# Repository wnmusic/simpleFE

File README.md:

# simpleFE
A very low cost mixed front end (ADC, DAC, SDR)

## Pre-requisite
simpleFE uses libusb, so a working libusb should be ready. Under linux, libusb also requires udev as the driver interface.  

If you would like to use gr-simplefe, you can install the latest gnuradio, gr-simplefe work as an out of tree module. Make it work on Windows is pretty involved. (please hack the CMakefiles to locate BOOST and CPPUnit)

For libdsp which is continously evolving, fftw3 is a must. 

## Install
```
# cd libsimplefe
# mkdir build
# cd build
# cmake ..
# make
# make install
```

for gr-smiplefe

```
# cd libsimplefe
# mkdir build
# cd build
# cmake ..
# make
# make install
```

## Load the firmware before you go
Right now, the firmware of simplefe is loaded via USB as well. The firmware leaves in firmware directory.  (There is no source for firmware, mainly because it is built based on the example code from Cypress, anyone interested in re-write it using sdcc, please contact me!)

You also have to build the fw\_load (which is done when built libsimplefe), it is in libsimplefe/build/example/fw\_load

```
#cd firmware
#../libsimplfe/build/example/fw\_load simpleFE.hex
```
D6 on simpleFE will be lit if firmware is sucessfuly loaded. 

## Make firmware autoload (Linux)
On linux, the firmware loading can be done by udev. 
```
#mkdir -p /usr/local/share/simplefe
```
Copy fw\_load and simpleFE.hex to /usr/local/share/simplefe. 

Then change 
```
GROUP=`groups | cut -f 1 -d ' '`
``` 
to your own group id by running the command in the quote in udev/99-udev-simplefe.rules. 

After that 
```
#cp udev/99-udev-simplefe.rules /etc/udev/rules.d
```
Next time when you plug in simpleFE D6 will be lit automatically.

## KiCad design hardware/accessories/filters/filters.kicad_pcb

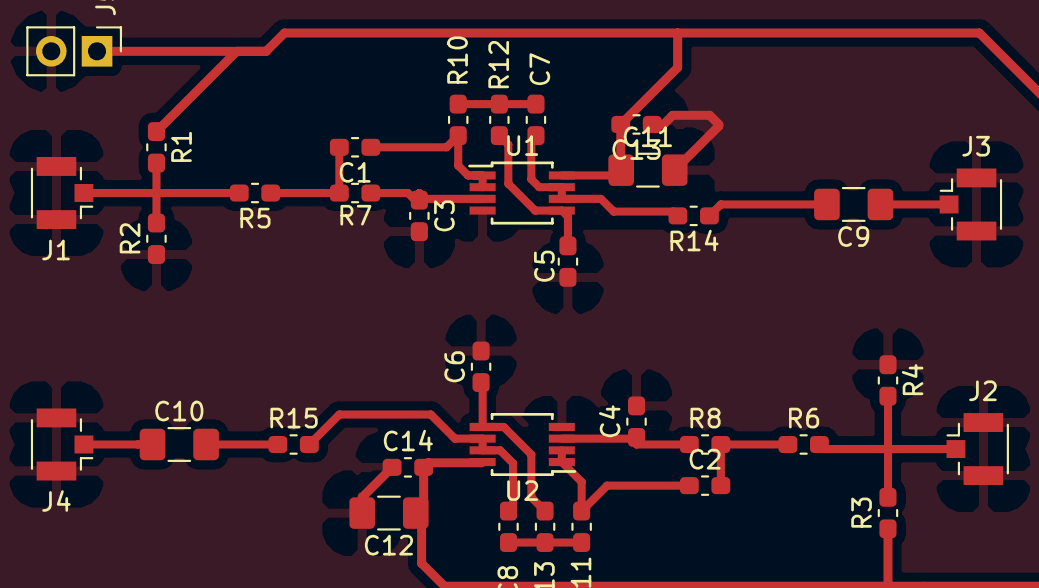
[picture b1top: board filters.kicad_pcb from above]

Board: 2 copper layers, 35 parts (0 on the bottom side), 20 nets.

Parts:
C1, C2: 150p; C_0603_1608Metric_Pad1.05x0.95mm_HandSolder
C3, C4: 120p; C_0603_1608Metric_Pad1.05x0.95mm_HandSolder
C5, C6: 56p; C_0603_1608Metric_Pad1.05x0.95mm_HandSolder
C7, C8: 390p; C_0603_1608Metric_Pad1.05x0.95mm_HandSolder
C9, C10, C11, C12: 10u; C_1206_3216Metric_Pad1.42x1.75mm_HandSolder
C13, C14: 100n; C_0603_1608Metric_Pad1.05x0.95mm_HandSolder
J1, J2, J3, J4: Conn_Coaxial; U.FL_Hirose_U.FL-R-SMT-1_Vertical
J5: PWR; PinHeader_1x02_P2.54mm_Vertical
R1, R2, R3, R4: 100k; R_0603_1608Metric_Pad1.05x0.95mm_HandSolder
R5, R6: 9.1k; R_0603_1608Metric_Pad1.05x0.95mm_HandSolder
R7, R8: 15k; R_0603_1608Metric_Pad1.05x0.95mm_HandSolder
R10, R11: 9.5k; R_0603_1608Metric_Pad1.05x0.95mm_HandSolder
R12, R13: 12k; R_0603_1608Metric_Pad1.05x0.95mm_HandSolder
R14, R15: 50; R_0603_1608Metric_Pad1.05x0.95mm_HandSolder
U1, U2: ada4891-2; MSOP-8_3x3mm_P0.65mm

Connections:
GND: C3.2, C4.2, C5.2, C6.2, C11.2, C12.2, C13.1, C14.1, J1.2, J2.2, J3.2, J4.2, J5.2, R2.1, R4.1, U1.4, U2.4
unnamed: C1.1, R10.2, U1.1, U1.2
unnamed: C1.2, R5.1, R7.2
unnamed: C2.1, R11.2, U2.1, U2.2
unnamed: C2.2, R6.1, R8.2
unnamed: C3.1, R7.1, U1.3
unnamed: C4.1, R8.1, U2.3
unnamed: C5.1, R12.1, U1.5
unnamed: C6.1, R13.1, U2.5
unnamed: C7.1, R14.2, U1.6, U1.7
unnamed: C7.2, R10.1, R12.2
unnamed: C8.1, R15.2, U2.6, U2.7
unnamed: C8.2, R11.1, R13.2
unnamed: C9.1, J3.1
unnamed: C9.2, R14.1
unnamed: C10.1, J4.1
unnamed: C10.2, R15.1
unnamed: J1.1, R1.2, R2.2, R5.2
unnamed: J2.1, R3.2, R4.2, R6.2
VCC: C11.1, C12.1, C13.2, C14.2, J5.1, R1.1, R3.1, U1.8, U2.8

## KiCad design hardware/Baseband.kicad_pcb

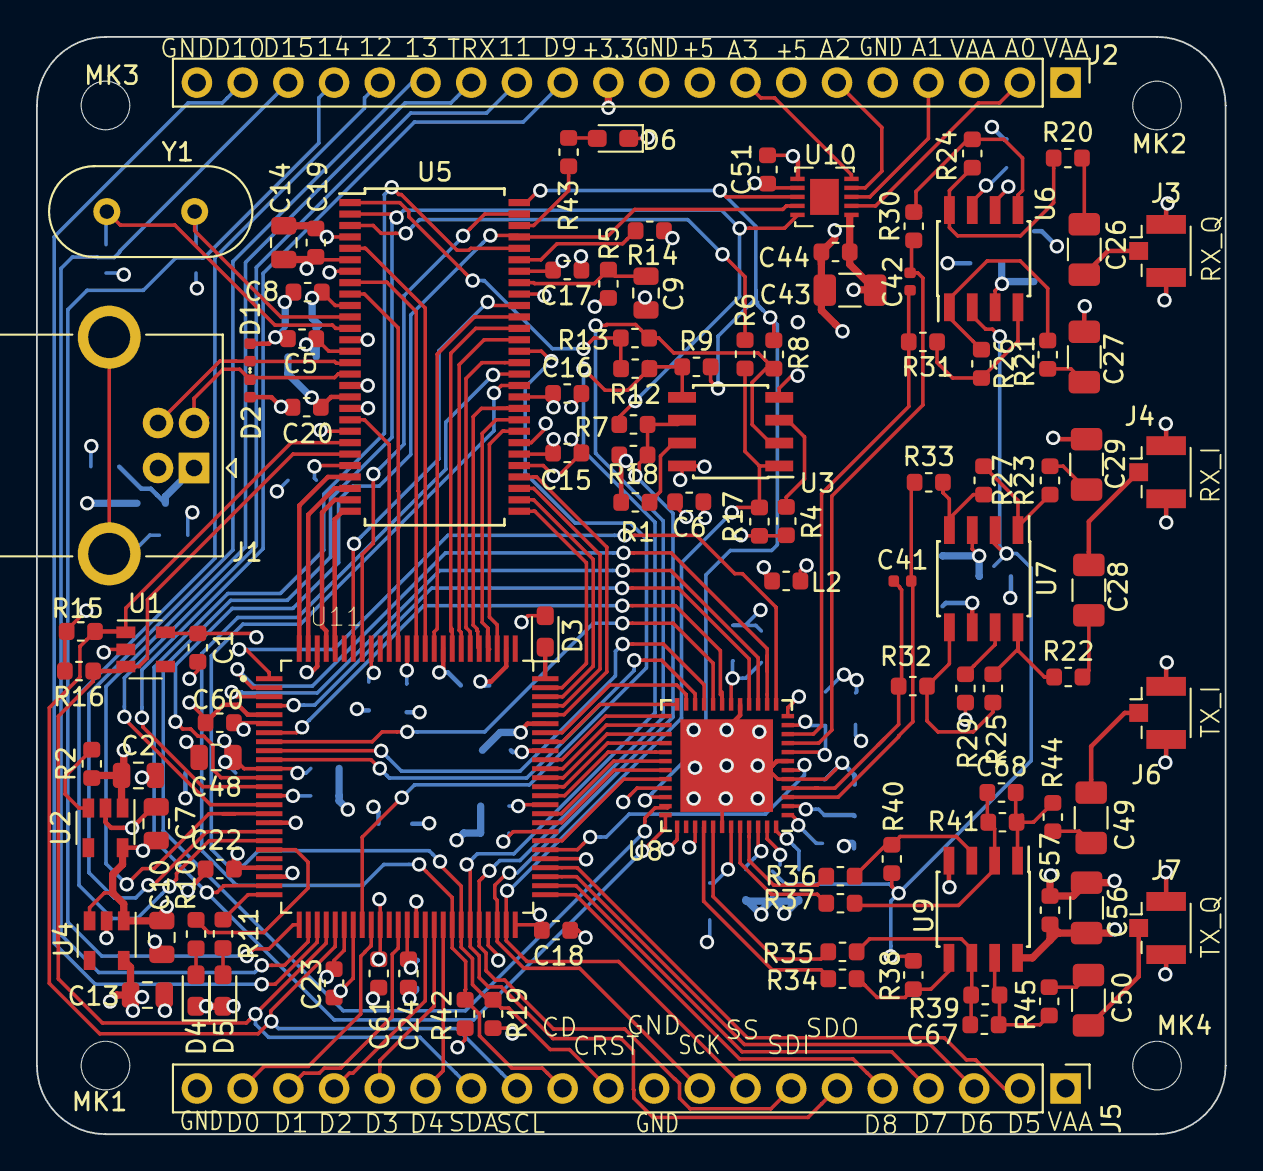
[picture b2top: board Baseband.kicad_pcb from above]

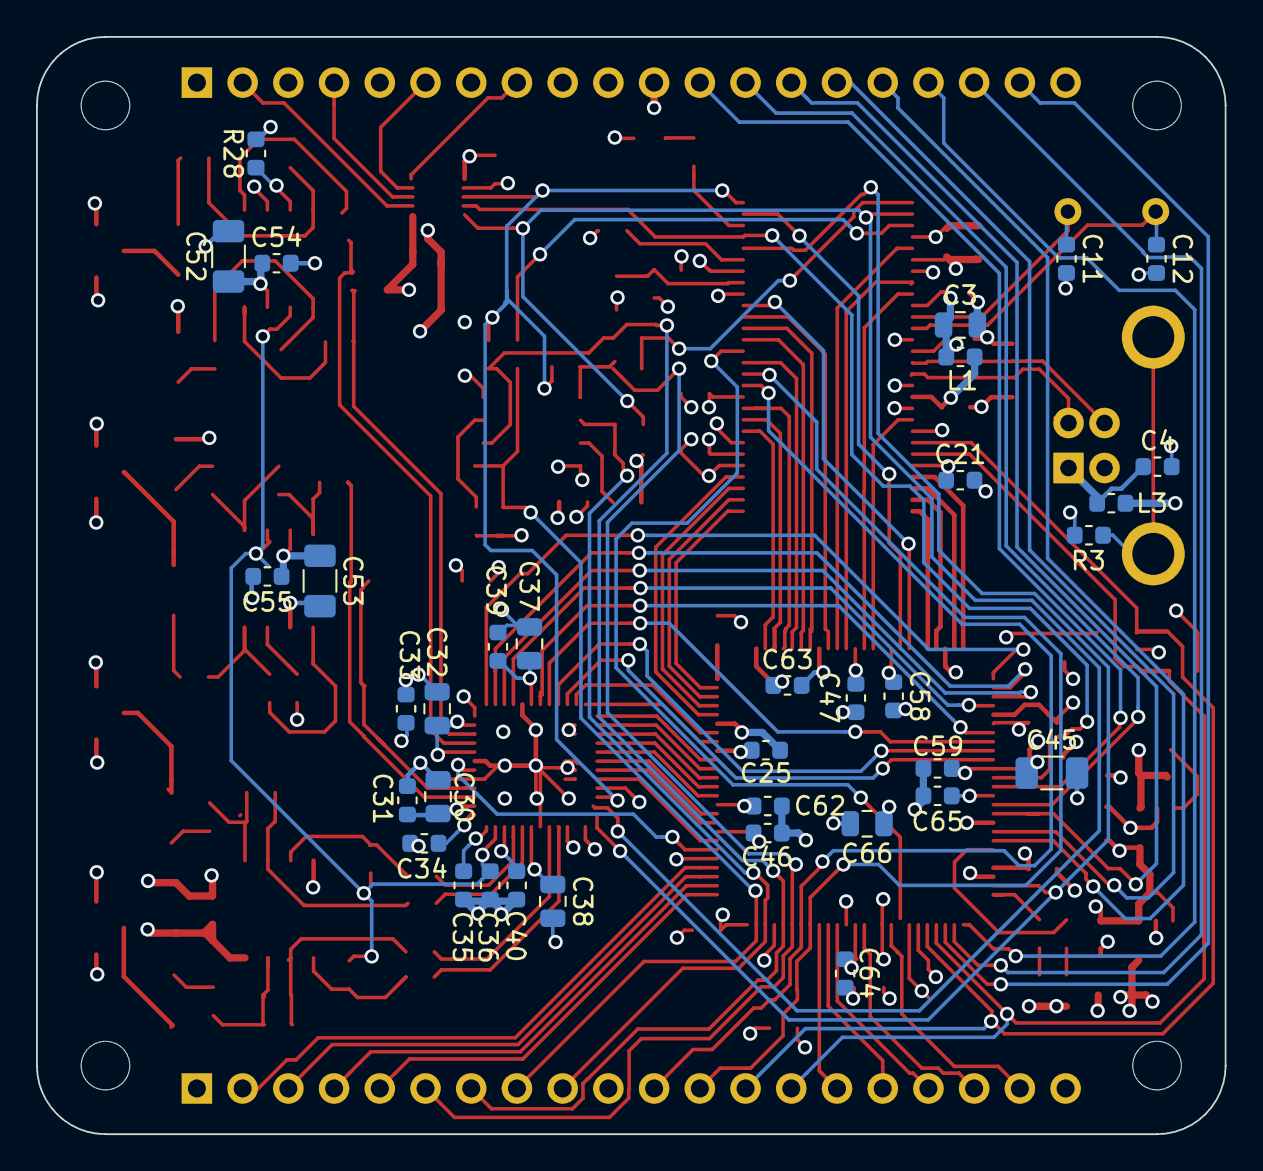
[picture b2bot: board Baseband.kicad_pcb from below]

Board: 4 copper layers, 66.0 x 61.0 mm, 145 parts (35 on the bottom side), 137 nets.

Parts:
C1, C5, C6, C8, C15, C16, C17, C18, C19, C20, C21, C22, C23, C24, C25, C31, C33, C39, C40, C44, C46, C47, C51, C54, C55, C57, C58, C59, C60, C61, C62, C63, C64, C65: 0.1u; C_0603_1608Metric
C2, C7, C9, C10, C13, C48, C66: 1u; C_0805_2012Metric
C3, C14: 4.7uF; C_0805_2012Metric
C4: 10nF; C_0603_1608Metric
C11, C12: 12p; C_0603_1608Metric
C26, C27, C28, C29, C43, C45, C49, C50, C52, C53, C56: 10u; C_1206_3216Metric
C30, C32, C37, C38: 2.2u; C_0805_2012Metric
C34, C35, C36: 0.33u; C_0603_1608Metric
C41, C42: 10p; C_0402_1005Metric
C67, C68: 2pF; C_0603_1608Metric
D1, D2: D_TVS; D_0402_1005Metric
D3: D; D_0603_1608Metric_Pad1.05x0.95mm_HandSolder
D4, D5, D6: LED; LED_0603_1608Metric_Pad1.05x0.95mm_HandSolder
J1: USB_B; USB_B_OST_USB-B1HSxx_Horizontal
J2, J5: Conn_01x20_Female; PinHeader_1x20_P2.54mm_Vertical
J3: RX_Q_IN; U.FL_Hirose_U.FL-R-SMT-1_Vertical
J4: RX_I_IN; U.FL_Hirose_U.FL-R-SMT-1_Vertical
J6: TX_I_OUT; U.FL_Hirose_U.FL-R-SMT-1_Vertical
J7: TX_Q_OUT; U.FL_Hirose_U.FL-R-SMT-1_Vertical
L1, L2, L3: BLM18KG601BH1D; L_0603_1608Metric
MK1, MK2, MK3, MK4: M2.5; MountingHole_2.7mm_M2.5
R1, R2, R4, R14, R17, R18, R19, R28, R29, R42: 10k; R_0603_1608Metric
R3, R6, R7, R8, R9, R12, R13: 0; R_0603_1608Metric
R5: 100k; R_0603_1608Metric
R10, R11, R43: 1k; R_0603_1608Metric
R15, R16: 2.2k; R_0603_1608Metric
R20, R21, R22, R23, R24, R25, R26, R27: 4.7k; R_0603_1608Metric
R30, R31, R32, R33: 50; R_0603_1608Metric
R34, R35, R36, R37, R38, R39, R40, R41: 4.7k%1; R_0603_1608Metric
R44, R45: 47k%1; R_0603_1608Metric
U1: 24LC00; SOT-23-5
U2: LP5907-3.3; SOT-23-5
U3: AT25SF041; SOIC-8_3.9x4.9mm_P1.27mm
U4: MIC5504-1.2YM5; SOT-23-5
U5: CY7C68013A-56PVX; SSOP-56_7.5x18.5mm_P0.635mm
U6, U7: AD8137; SOIC-8_3.9x4.9mm_P1.27mm
U8: MAX5863; QFN-48-1EP_7x7mm_P0.5mm_EP5.15x5.15mm
U9: ADA4891-2; SOIC-8_3.9x4.9mm_P1.27mm
U10: DAC084S085; Texas_DSC0010A
U11: ICE40HX1K-VQ100; QFP50P1600X1600X120-100N
Y1: 24M; Crystal_HC49-U_Vertical

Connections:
+1V2: C13.1, C45.1, C48.1, C59.1, C61.1, C62.1, C63.1, C66.1, U4.5, U11.11, U11.35, U11.61, U11.77
+3V3: C1.1, C6.1, C7.1, C10.1, C14.1, C15.1, C16.1, C17.1, C18.1, C19.1, C20.1, C21.1, C22.1, C23.1, C24.1, C25.1, C37.1, C39.1, C46.1, C47.1, C58.1, C60.1, C64.1, C65.1, D3.2, J2.11, L1.1, L2.1, R1.1, R4.1, R5.1, R14.1, R15.2, R16.2, R17.1, R18.1, R19.1, R42.1, U1.5, U2.5, U3.8, U4.1, U4.3, U5.6, U5.18, U5.24, U5.34, U5.39, U5.50, U8.18, U11.6, U11.14, U11.22, U11.31, U11.38, U11.50, U11.58, U11.67, U11.88, U11.92
+5V: C2.1, J2.7, J2.9, L3.2, R2.1, U2.1
/ADC_VCOM: C36.2, R38.2, R40.2, U6.2, U7.2, U8.47
/AUX_AO0: J2.2, U10.2
/AUX_AO1: J2.4, U10.3
/AUX_AO2: J2.6, U10.4
/AUX_AO3: J2.8, U10.5
/CLKOUT: U5.5, U11.86
/CY_AVCC: C3.1, C5.1, C8.1, L1.2, U5.10, U5.14
/CY_SCK: R7.2, U5.2, U8.35, U10.10
/CY_SDI: R12.2, R13.2, U5.1
/CY_SDO: R8.2, R9.2, U5.56, U8.34, U10.8
/CY_SS: R6.2, U5.3
/D0: U5.25, U11.100
/D1: U5.26, U11.99
/D2: U5.27, U11.97
/D3: U5.28, U11.96
/D4: U5.29, U11.74
/D5: U5.30, U11.73
/D6: U5.31, U11.72
/D7: U5.32, U11.71
/DA0: U8.13, U11.1
/DA1: U8.14, U11.2
/DA2: U8.15, U11.3
/DA3: U8.16, U11.4
/DA4: U8.19, U11.7
/DA5: U8.20, U11.8
/DA6: U8.21, U11.9
/DA7: U8.22, U11.10
/DD0: U8.23, U11.69
/DD1: U8.24, U11.68
/DD2: U8.25, U11.66
/DD3: U8.26, U11.65
/DD4: U8.27, U11.64
/DD5: U8.28, U11.63
/DD6: U8.29, U11.62
/DD7: U8.30, U11.60
/DD8: U8.31, U11.59
/DD9: U8.32, U11.57
/DIO0: J5.19, U11.34
/DIO1: J5.18, U11.37
/DIO2: J5.17, U11.40
/DIO3: J5.16, U11.41
/DIO4: J5.15, U11.42
/DIO5: J5.2, U11.54
/DIO6: J5.3, U11.53
/DIO7: J5.4, U11.52
/DIO8: J5.5, U11.51
/DIO9: J2.12, U11.13
/DIO10: J2.19, U11.28
/DIO11: J2.13, U11.15
/DIO12: J2.16, U11.19
/DIO13: J2.15, U11.18
/DIO14: J2.17, U11.26
/DIO15: J2.18, U11.27
/FIFOADDR[0]: U5.44, U11.82
/FIFOADDR[1]: U5.45, U11.83
/FLAGA: U5.36, U11.78
/FLAGB: U5.37, U11.79
/FLAGC: U5.38, U11.80
/IA+: C41.2, R33.1, U8.3
/IA-: C41.1, R32.1, U8.4
/ICE_CDONE: J5.12, R42.2, U5.41, U11.43
/ICE_CRESETB: J5.11, R19.2, U5.40, U11.44
/ICE_SCK: J5.9, R7.1, R18.2, U3.6, U11.48
/ICE_SDI: J5.7, R8.1, R13.1, U3.2, U11.46
/ICE_SDO: J5.6, R9.1, R12.1, U3.5, U11.45
/ICE_SS: J5.8, R6.1, R17.2, U3.1, U11.49
/ID+: R36.2, U8.45
/ID-: R37.2, U8.44
/IFCLK: U5.20, U11.90
/MAX_CLK: U8.6, U11.56
/PA3: U5.43, U11.33
/PD0: U5.52, U8.36, U11.24
/PD1: U5.53, U10.9, U11.12
/PD2: R43.2, U5.54
/PD3: U5.55, U11.93
/PKTEND: U5.46, U11.85
/QA+: C42.2, R31.1, U8.10
/QA-: C42.1, R30.1, U8.9
/QD+: R34.2, U8.40
/QD-: R35.2, U8.41
/RX_I: C28.2, J4.1
/RX_Q: C26.2, J3.1
/SCL: J5.13, R15.1, U1.1, U5.22, U11.30
/SDA: J5.14, R16.1, U1.3, U5.23, U11.29
/SLOE: U5.42, U11.81
/SLRD: U5.8, U11.87
/SLWR: U5.9, U11.89
/TXRX#: J2.14, U11.16
/TX_I: C49.1, J6.1
/TX_Q: C50.1, J7.1
/USB_D+: D1.1, J1.3, U5.15
/USB_D-: D2.1, J1.2, U5.16
/~SLCS: U5.47, U11.94
GND: C1.2, C2.2, C3.2, C4.2, C5.2, C6.2, C7.2, C8.2, C9.2, C10.2, C11.2, C12.2, C13.2, C14.2, C15.2, C16.2, C17.2, C18.2, C19.2, C20.2, C21.2, C22.2, C23.2, C24.2, C25.2, C27.2, C29.2, C30.2, C31.2, C32.2, C33.2, C34.2, C35.1, C36.1, C37.2, C38.2, C39.2, C40.2, C43.2, C44.2, C45.2, C46.2, C47.2, C48.2, C51.2, C52.2, C53.2, C54.2, C55.2, C56.2, C57.2, C58.2, C59.2, C60.2, C61.2, C62.2, C63.2, C64.2, C65.2, C66.2, D1.2, D2.2, D4.1, D5.1, D6.1, J1.4, J2.5, J2.10, J2.20, J3.2, J4.2, J5.10, J5.20, J6.2, J7.2, R3.1, U1.2, U2.2, U3.4, U4.2, U5.4, U5.7, U5.13, U5.17, U5.19, U5.21, U5.33, U5.35, U5.48, U6.6, U7.6, U8.5, U8.7, U8.12, U8.17, U8.37, U8.42, U8.49, U9.4, U10.6, U11.5, U11.17, U11.23, U11.32, U11.39, U11.47, U11.55, U11.70, U11.84, U11.98
unnamed: C9.1, R5.2, U5.49
unnamed: C11.1, U5.11, Y1.1
unnamed: C12.1, U5.12, Y1.2
unnamed: C26.1, R20.2
unnamed: C27.1, R21.2
unnamed: C28.1, R22.2
unnamed: C29.1, R23.2
unnamed: C34.1, U8.1
unnamed: C35.2, U8.48
unnamed: C49.2, R44.1
unnamed: C50.2, R45.1
unnamed: C67.1, R35.1, R39.2, U9.6
unnamed: C67.2, R39.1, R45.2, U9.7
unnamed: C68.1, R37.1, R41.2, U9.2
unnamed: C68.2, R41.1, R44.2, U9.1
unnamed: D3.1, U11.75
unnamed: D4.2, R10.2
unnamed: D5.2, R11.2
unnamed: D6.2, R43.1
unnamed: J1.5, R3.2
unnamed: R1.2, U3.7
unnamed: R2.2, U2.3
unnamed: R4.2, U3.3
unnamed: R10.1, U11.20
unnamed: R11.1, U11.25
unnamed: R14.2, U5.51
unnamed: R20.1, R24.2, U6.8
unnamed: R21.1, R26.2, U6.1
unnamed: R22.1, R25.2, U7.8
unnamed: R23.1, R27.2, U7.1
unnamed: R24.1, R30.2, U6.5
unnamed: R25.1, R32.2, U7.5
unnamed: R26.1, R31.2, U6.4
unnamed: R27.1, R33.2, U7.4
unnamed: R28.2, U6.7
unnamed: R29.2, U7.7
unnamed: R34.1, R38.1, U9.5
unnamed: R36.1, R40.1, U9.3
VBUS: C4.1, J1.1, L3.1
VDDA3: C30.1, C31.1, C32.1, C33.1, C38.1, C40.1, C43.1, C44.1, C51.1, C52.1, C53.1, C54.1, C55.1, C56.1, C57.1, J2.1, J2.3, J5.1, L2.2, R28.1, R29.1, U6.3, U7.3, U8.2, U8.8, U8.11, U8.33, U8.39, U8.43, U8.46, U9.8, U10.1, U10.7

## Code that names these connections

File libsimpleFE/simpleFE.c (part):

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                )
{

    int tx_i=0,  tx_q=0;
    unsigned clk, rate;


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                  )
{

    int rx_i=0,  rx_q=0;
    const unsigned th = 1024 *num_pkts_per_sec;
    
    h->rx_pkts = 0;
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
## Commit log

2019-09-20 checkin lib
2019-09-20 add gnuradio componenet
2019-09-20 add sch
2019-09-23 remove warnings change link order in cmakefiles
2019-09-23 make osx also compile
2019-09-23 change the libsimpleFE location
2019-10-03 make load program
2019-10-03 add firmware binary'
2019-10-08 add hardware source files
2019-10-18 add libdsp
2019-10-21 add bpsk example
2019-10-21 add a filter design
2019-10-22 Create top_bitmap.hex
    add fpga bitmap
2019-10-22 Create top_bitmap.bin
    add fpga bin file
2019-10-31 get filter pcb
2019-11-03 update the filter sch
2019-11-04 add a test RC filter
2019-11-04 add a bit of doc
2019-11-11 minor change
2019-11-18 add a resampler
2019-11-19 add testing code for resample
2019-11-19 should make the last sample right
2019-11-20 fix issues on resampling
2019-11-21 more bug fixes
2019-11-25 add another decimator
2019-11-25 add decimator and test
2020-02-19 add external GPIO set function
2020-02-19 add usb transfer function
2020-02-19 adding i2c support
2020-04-12 add external spi example
2020-04-12 add adf4360-7 as an example
2020-04-14 fix bugs on i2c and use i2c for gpio
2020-04-15 add a delay on PLL example
2021-12-01 commit various changes, adding a PLL divider to fpga

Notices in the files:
libsimpleFE/simpleFE.c:
Copyright (c) 2019, Ning Wang <nwang.cooper@gmail.com> All rights reserved.
hardware/Baseband.kicad_pcb:
License: GPLv2\
